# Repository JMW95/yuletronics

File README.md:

# Yuletronics: Electronics Club Project Michaelmas 2016

A small electronic Christmas decoration with a 5x5 pixel LED screen.

Scrolls festive messages across the screen, and plays Flappy Bird!

Firmware written in C using ChibiOS for the STM32F042F6P6 microcontroller.
PCB designed in KiCAD. Download it [here](http://kicad-pcb.org/).

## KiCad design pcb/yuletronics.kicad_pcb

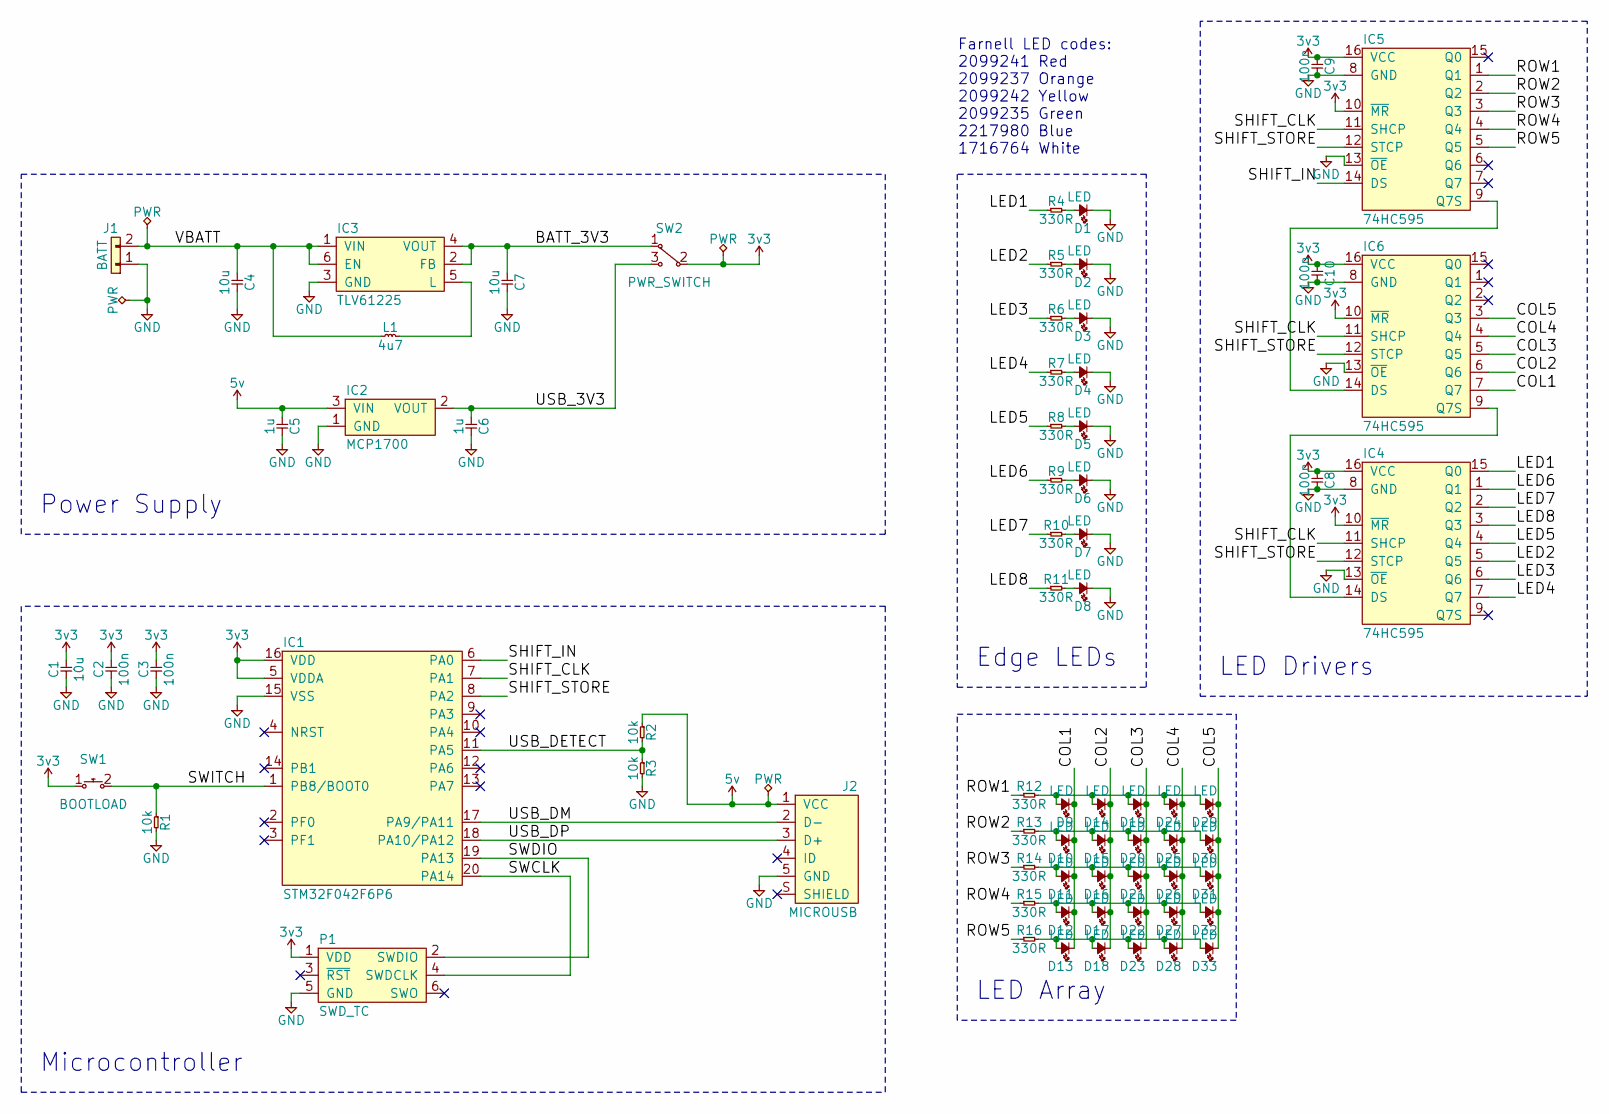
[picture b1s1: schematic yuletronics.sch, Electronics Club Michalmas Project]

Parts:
C1, C4, C7: 10u; 0603; Farnell 2494230
C2, C3, C8, C9, C10: 100n; 0603; Farnell 1759038
C5, C6: 1u; 0603; Farnell 1759399
D1, D8: LED; 0805-LED; Farnell 2099242
D2, D5: LED; 0805-LED; Farnell 2217980
D3: LED; 0805-LED; Farnell 2099235
D4: LED; KPA-1606; Farnell 2290355
D6: LED; KPA-1606; Farnell 2290360
D7: LED; 0805-LED; Farnell 2099241
D9, D10, D11, D12, D13, D14, D15, D16, D17, D18, D19, D20, D21, D22, D23, D24, D25, D26, D27, D28, D29, D30, D31, D32, D33: LED; KPT-1608; Farnell 2099221
IC1: STM32F042F6P6; TSSOP-20; Farnell 2469549
IC2: MCP1700; SOT-23; Farnell 1296592
IC3: TLV61225; SC-70-6; Farnell 2492362
IC4, IC5, IC6: 74HC595; TSSOP-16; Farnell 2425499
J1: BATT; AAA_HOLDER; Farnell 1702632
J2: MICROUSB; MICROUSB_MOLEX_47589-0001; Farnell 1568023
L1: 4u7; 2016M; Farnell 2616849
P1: SWD_TC; TC2030-NL
R1, R2, R3: 10k; 0603; Farnell 9330399
R4, R5, R6, R7, R8, R9, R10, R11, R12, R13, R14, R15, R16: 330R; 0603; Farnell 9331018
SW1: BOOTLOAD; MOM_SWITCH; Farnell 2056809
SW2: PWR_SWITCH; SPDT_SWITCH; Farnell 1201430

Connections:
3v3: C1.2, C2.2, C3.2, C8.1, C9.1, C10.1, IC1.5 (VDDA), IC1.16 (VDD), IC4.10 (~MR), IC4.16 (VCC), IC5.10 (~MR), IC5.16 (VCC), IC6.10 (~MR), IC6.16 (VCC), P1.1 (VDD), SW1.1, SW2.2
5v: C5.1, IC2.3 (VIN), J2.1 (VCC), R2.1
/BATT_3V3: C7.1, IC3.2 (FB), IC3.4 (VOUT), SW2.1
/COL1: D9.1, D10.1, D11.1, D12.1, D13.1, IC6.7 (Q7)
/COL2: D14.1, D15.1, D16.1, D17.1, D18.1, IC6.6 (Q6)
/COL3: D19.1, D20.1, D21.1, D22.1, D23.1, IC6.5 (Q5)
/COL4: D24.1, D25.1, D26.1, D27.1, D28.1, IC6.4 (Q4)
/COL5: D29.1, D30.1, D31.1, D32.1, D33.1, IC6.3 (Q3)
/LED1: IC4.15 (Q0), R4.1
/LED2: IC4.5 (Q5), R5.1
/LED3: IC4.6 (Q6), R6.1
/LED4: IC4.7 (Q7), R7.1
/LED5: IC4.4 (Q4), R8.1
/LED6: IC4.1 (Q1), R9.1
/LED7: IC4.2 (Q2), R10.1
/LED8: IC4.3 (Q3), R11.1
/ROW1: IC5.1 (Q1), R12.1
/ROW2: IC5.2 (Q2), R13.1
/ROW3: IC5.3 (Q3), R14.1
/ROW4: IC5.4 (Q4), R15.1
/ROW5: IC5.5 (Q5), R16.1
/SHIFT_CLK: IC1.7 (PA1), IC4.11 (SHCP), IC5.11 (SHCP), IC6.11 (SHCP)
/SHIFT_IN: IC1.6 (PA0), IC5.14 (DS)
/SHIFT_STORE: IC1.8 (PA2), IC4.12 (STCP), IC5.12 (STCP), IC6.12 (STCP)
/SWCLK: IC1.20 (PA14), P1.4 (SWDCLK)
/SWDIO: IC1.19 (PA13), P1.2 (SWDIO)
/SWITCH: IC1.1 (PB8/BOOT0), R1.1, SW1.2
/USB_3V3: C6.1, IC2.2 (VOUT), SW2.3
/USB_DETECT: IC1.11 (PA5), R2.2, R3.1
/USB_DM: IC1.17 (PA9/PA11), J2.2 (D-)
/USB_DP: IC1.18 (PA10/PA12), J2.3 (D+)
/VBATT: C4.1, IC3.1 (VIN), IC3.6 (EN), J1.2, L1.1
GND: C1.1, C2.1, C3.1, C4.2, C5.2, C6.2, C7.2, C8.2, C9.2, C10.2, D1.1, D2.1, D3.1, D4.1, D5.1, D6.1, D7.1, D8.1, IC1.15 (VSS), IC2.1 (GND), IC3.3 (GND), IC4.8 (GND), IC4.13 (~OE), IC5.8 (GND), IC5.13 (~OE), IC6.8 (GND), IC6.13 (~OE), J1.1, J2.5 (GND), P1.5 (GND), R1.2, R3.2
unnamed: D1.2, R4.2
unnamed: D2.2, R5.2
unnamed: D3.2, R6.2
unnamed: D4.2, R7.2
unnamed: D5.2, R8.2
unnamed: D6.2, R9.2
unnamed: D7.2, R10.2
unnamed: D8.2, R11.2
unnamed: D10.2, D15.2, D20.2, D25.2, D30.2, R13.2
unnamed: D11.2, D16.2, D21.2, D26.2, D31.2, R14.2
unnamed: D12.2, D17.2, D22.2, D27.2, D32.2, R15.2
unnamed: D13.2, D18.2, D23.2, D28.2, D33.2, R16.2
unnamed: D9.2, D14.2, D19.2, D24.2, D29.2, R12.2
unnamed: IC3.5 (L), L1.2
unnamed: IC4.14 (DS), IC6.9 (Q7S)
unnamed: IC5.9 (Q7S), IC6.14 (DS)

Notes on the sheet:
Power Supply
Microcontroller
Edge LEDs
Farnell LED codes: 2099241 Red 2099237 Orange 2099242 Yellow 2099235 Green 2217980 Blue 1716764 White
LED Drivers
LED Array

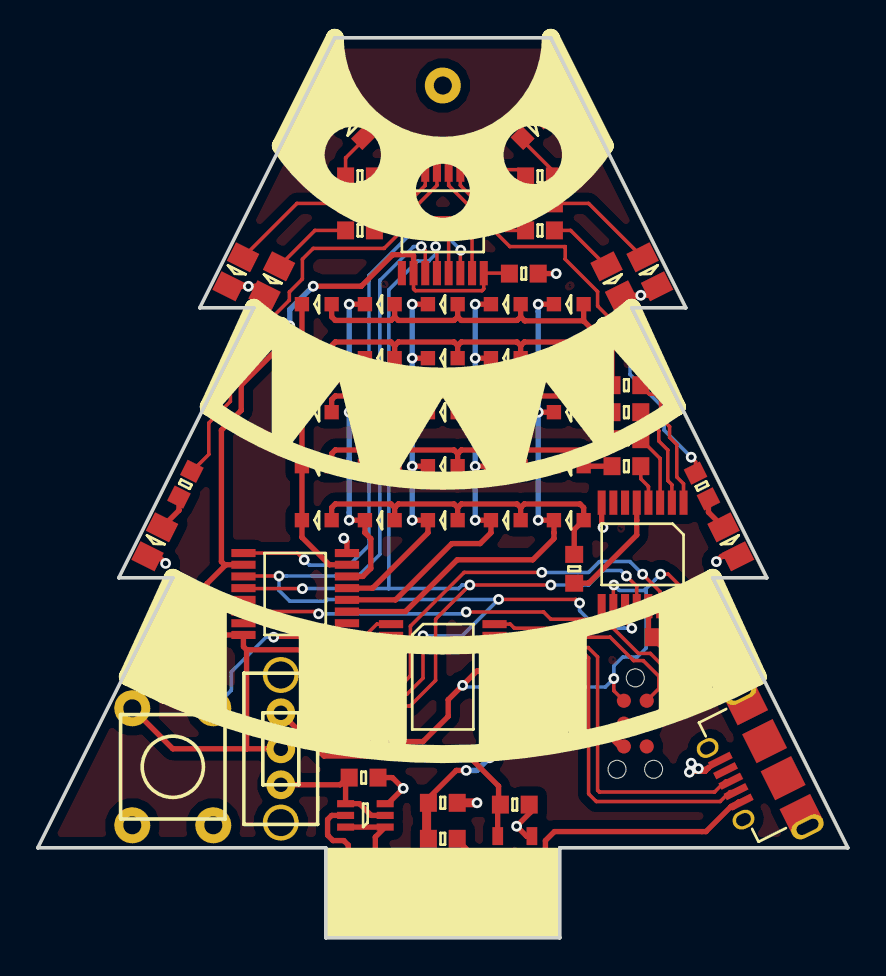
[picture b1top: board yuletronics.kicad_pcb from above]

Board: 2 copper layers, 45.0 x 50.0 mm, 71 parts (1 on the bottom side), 49 nets.

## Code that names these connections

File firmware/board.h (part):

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/*
 *  GPIOA setup:
 *
 * PA0  - SHIFT_DATA                   (output, pushpull, startlow).
 * PA1  - SHIFT_CLK                    (output, pushpull, startlow).
 * PA2  - SHIFT_LATCH                  (output, pushpull, startlow).
 * PA3  - PIN3                         (unused).
 * PA4  - PIN4                         (unused).
 * PA5  - USB_DETECT                   (analog).
 * PA6  - PIN6                         (unused).
 * PA7  - PIN7                         (unused).
 * PA8  - PIN8                         (unused).
 * PA9  - PIN9                         (unused).
 * PA10 - PIN10                        (unused).
 * PA11 - PIN11                        (unused).
 * PA12 - PIN12                        (unused).
 * PA13 - SWDIO                        (af0, pulldown).
 * PA14 - SWDCLK                       (af0, pulldown).
 * PA15 - PIN15                        (unused).
*/
#define VAL_GPIOA_MODER                (PIN_MODE_OUTPUT(GPIOA_SHIFT_DATA) | \
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 * PB5  - PIN5                         (unused).
 * PB6  - PIN6                         (unused).
 * PB7  - PIN7                         (unused).
 * PB8  - SWITCH                       (input, floating).
 * PB9  - PIN9                         (unused).
 * PB10 - PIN10                        (unused).
 * PB11 - PIN11                        (unused).
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
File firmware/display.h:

#ifndef DISPLAY_H
#define DISPLAY_H

#include "ch.h"

// LED numbers as bits in the shift register
#define LED1    0
#define LED2    5
#define LED3    6
#define LED4    7
#define LED5    4
#define LED6    1
#define LED7    2
#define LED8    3

void display_init(void);
void display_scroll_text(const char *str);
void display_set_anim(uint8_t idx);
bool display_scroll(void);
bool display_anim(void);
void display_clear(void);
void display_copy(uint8_t data[]);
void display_show(void);

void led_turn_on(int which);
void led_turn_off(int which);

#endif /* DISPLAY_H */

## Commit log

2016-11-01 Add LED array
2016-11-09 Add firmware
2016-11-09 Add gerbers, fix DRC
2016-11-14 Add shiftreg driver
2016-11-14 Fix board and mcu setup
2016-11-14 Add basic font
2016-11-14 Add basic functionality
2016-11-18 Fix initial state of outputs
2016-11-18 Fix compile errors
2016-11-30 Add stencil dxf
2016-11-30 Fix Makefile
2016-11-30 Fix display offset
2016-11-30 Fix font rotation
2016-11-30 Fix rotation of font table
2016-11-30 Add scrolling text
2016-11-30 Fix message scrolling
2016-12-01 Add software PWM
2016-12-01 Add multiple messages
2016-12-01 Fix line endings
2016-12-01 Change pwm_tick to a single value
2016-12-01 Refactor display_update
2016-12-01 Add animations
2016-12-03 Change scroll speed
2016-12-05 Add switch to board.yaml/.h
2016-12-05 Add easter egg
2016-12-06 Start of USB work
2016-12-06 Add USB Serial printing
2016-12-07 Reduce code footprint by disabling ChibiOS features
2016-12-07 Add serial receiving, scroll lines read
2016-12-12 Change to ticked mode to reduce power draw a bit
2016-12-12 Add #define to enable USB
2016-12-12 Add low-power mode
2016-12-12 Reduce to 16MHz SYSCLK
2016-12-12 Move config to its own file
2016-12-12 Reduce SYSCLK to 8Mhz, turn off other clocks
2017-01-03 Remove README
2017-01-03 Cleanup old files
2018-04-16 Update USB

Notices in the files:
firmware/board.h:
ChibiOS - Copyright (C) 2006..2016 Giovanni Di Sirio
Licensed under the Apache License, Version 2.0 (the "License");
